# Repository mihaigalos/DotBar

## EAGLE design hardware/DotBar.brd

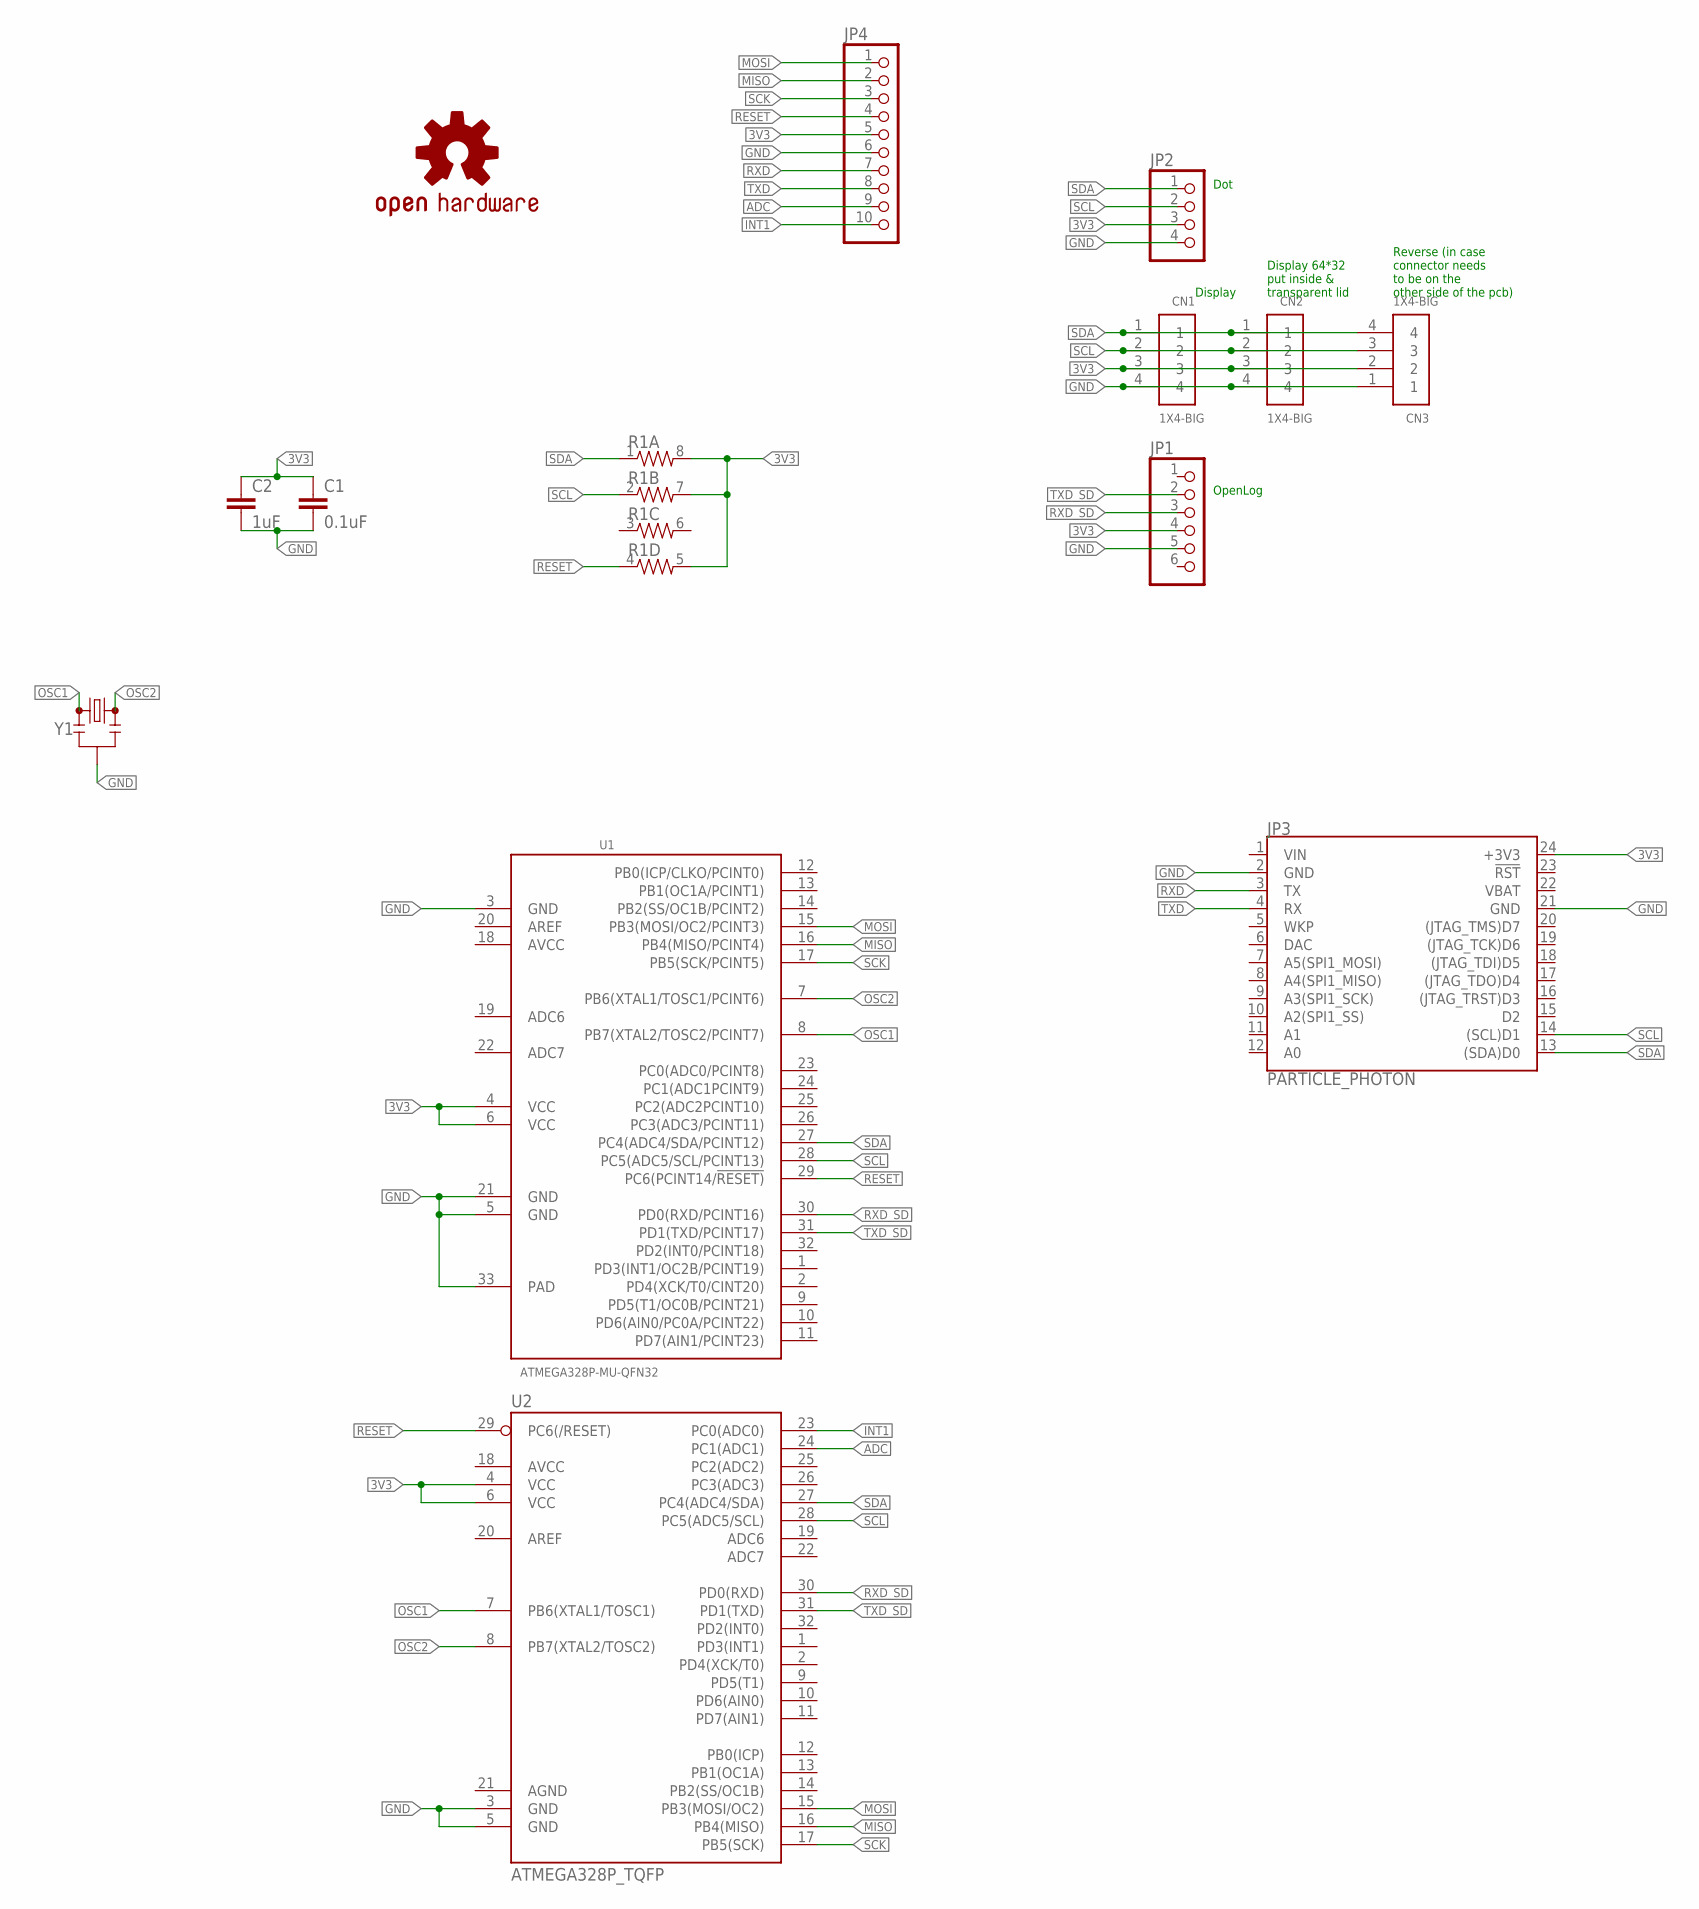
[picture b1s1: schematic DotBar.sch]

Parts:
C1: 0.1uF; C0603
C2: 1uF; C0603
CN1, CN2, CN3: 1X4-BIG; 1X04-BIG
JP1: PINHD-1X6; 1X06
JP2: PINHD-1X4; 1X04
JP3: PARTICLE_PHOTON
JP4: PINHD-1X10; 1X10
LOGO1: OSHW-LOGOS; OSHW-LOGO-S
R1: RESISTOR-ARRAY0603-ARV; 0603-ARV
U1: ATMEGA328P-MU-QFN32; QFN32G-0.5-5X5MM
U2: ATMEGA328P_TQFP; TQFP32-08
Y1: RESONATORSMD-3.2X1.3; RESONATOR-SMD-3.2X1.3

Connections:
3V3: C1.1, C2.1, CN1.3, CN2.3, CN3.2, JP1.4, JP2.3, JP3.24 (+3V3), JP4.5, R1.5 (2), R1.7 (2), R1.8 (2), U1.4 (VCC), U1.6 (VCC), U2.4 (VCC), U2.6 (VCC)
ADC: JP4.9, U2.24 (PC1(ADC1))
GND: C1.2, C2.2, CN1.4, CN2.4, CN3.1, JP1.5, JP2.4, JP3.2 (GND), JP3.21 (GND), JP4.6, U1.3 (GND), U1.5 (GND), U1.21 (GND), U1.33 (PAD), U2.3 (GND), U2.5 (GND), Y1.2
INT1: JP4.10, U2.23 (PC0(ADC0))
MISO: JP4.2, U1.16 (PB4(MISO/PCINT4)), U2.16 (PB4(MISO))
MOSI: JP4.1, U1.15 (PB3(MOSI/OC2/PCINT3)), U2.15 (PB3(MOSI/OC2))
OSC1: U1.8 (PB7(XTAL2/TOSC2/PCINT7)), U2.7 (PB6(XTAL1/TOSC1)), Y1.1
OSC2: U1.7 (PB6(XTAL1/TOSC1/PCINT6)), U2.8 (PB7(XTAL2/TOSC2)), Y1.3
RESET: JP4.4, R1.4 (1), U1.29 (PC6(PCINT14/!RESET)), U2.29 (PC6(/RESET))
RXD: JP3.3 (TX), JP4.7
RXD_SD: JP1.3, U1.30 (PD0(RXD/PCINT16)), U2.30 (PD0(RXD))
SCK: JP4.3, U1.17 (PB5(SCK/PCINT5)), U2.17 (PB5(SCK))
SCL: CN1.2, CN2.2, CN3.3, JP2.2, JP3.14 ((SCL)D1), R1.2 (1), U1.28 (PC5(ADC5/SCL/PCINT13)), U2.28 (PC5(ADC5/SCL))
SDA: CN1.1, CN2.1, CN3.4, JP2.1, JP3.13 ((SDA)D0), R1.1, U1.27 (PC4(ADC4/SDA/PCINT12)), U2.27 (PC4(ADC4/SDA))
TXD: JP3.4 (RX), JP4.8
TXD_SD: JP1.2, U1.31 (PD1(TXD/PCINT17)), U2.31 (PD1(TXD))
VBAT: JP3.22 (VBAT)
VIN: JP3.1 (VIN)

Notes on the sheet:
Display
Dot
OpenLog
Display 64*32 put inside & transparent lid
Reverse (in case connector needs to be on the other side of the pcb)

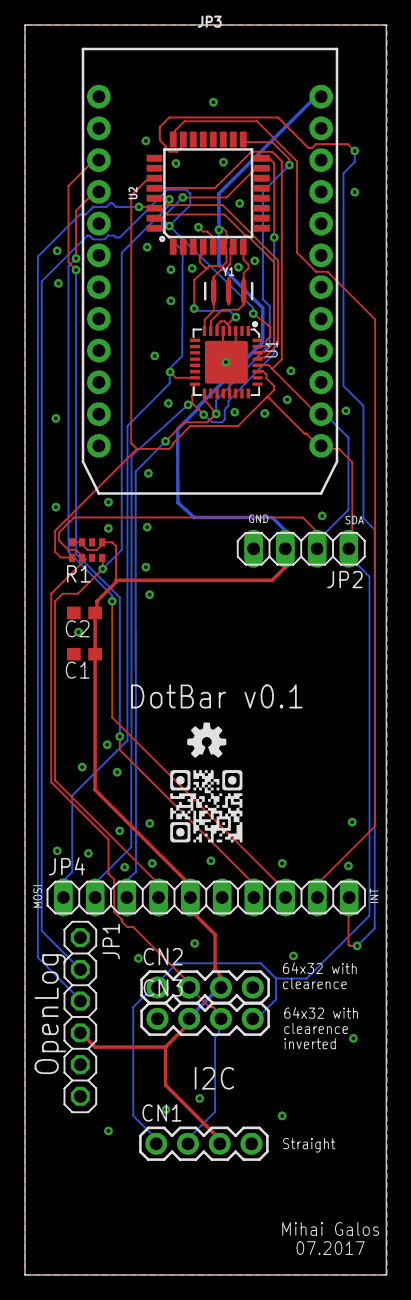
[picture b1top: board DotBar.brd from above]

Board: 2 copper layers, 28.9 x 100.0 mm, 14 parts (0 on the bottom side), 16 nets.

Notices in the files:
parts and their libraries:
SparkFun-IC-Microcontroller: Licensing: Creative Commons ShareAlike 4.0 International - https://creativecommons.org/licenses/by-sa/4.0
SparkFun: Licensing: CC v3.0 Share-Alike You are welcome to use this library for commercial purposes.
